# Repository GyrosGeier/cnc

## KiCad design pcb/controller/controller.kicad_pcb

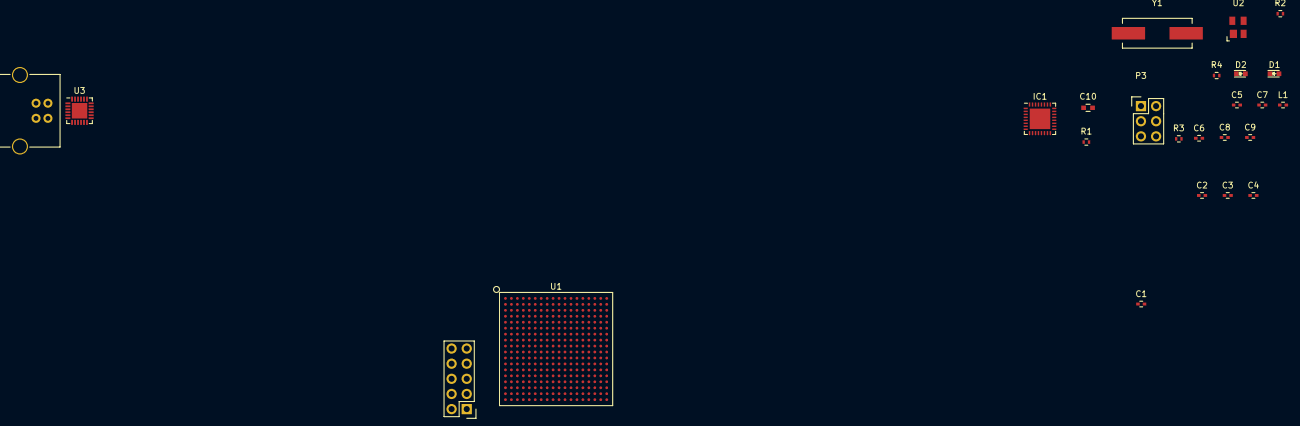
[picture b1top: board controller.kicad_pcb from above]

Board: 2 copper layers, 25 parts (0 on the bottom side), 25 nets, no tracks yet.

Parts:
C1, C2, C3, C4, C5, C6, C8: 100n; C_0402
C7, C9: 18pF; C_0402
C10: 4,7u; C_0603
D1, D2: orange; LED_0603
IC1: ATMEGA328P-M; QFN-32-1EP_5x5mm_Pitch0.5mm
L1: 1u; C_0402
P1: CONN_02X05; Pin_Header_Straight_2x05
P2: USB_B
P3: CONN_02X03; Pin_Header_Straight_2x03
R1, R2: 10k; R_0402
R3, R4: 60; R_0402
U1: EPM2210F324; BGA-324-1mm
U2: DRTR5V0U2SR; SOT-143
U3: CP2104; QFN-24-1EP_4x4mm_Pitch0.5mm
Y1: 16 MHz/18pF; Crystal_HC49-SD_SMD

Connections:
+3V3: C1.1, C2.1, C3.1, C4.1, C5.1, IC1.4, IC1.6, L1.1, P1.4, P3.2, R1.1, R2.2, R3.1, R4.1, U1.C1, U1.J7, U1.K7, U1.T1, U3.5
/GRBL/Arduino/0: IC1.30, U3.21
/GRBL/Arduino/1: IC1.31, U3.20
/GRBL/Arduino/DTR: C8.2, U3.23
/GRBL/Arduino/USB_D+: P2.3, U2.3, U3.3
/GRBL/Arduino/USB_D-: P2.2, U2.2, U3.4
/GRBL/Arduino/USB_VCC: P2.1, U2.4, U3.7, U3.8
/GRBL/Arduino/XI: C7.1, IC1.7, Y1.1
/GRBL/Arduino/XO: C9.1, IC1.8, Y1.2
/GRBL/SPINDLE_DIR: IC1.17, P3.3
/GRBL/SPINDLE_PWM: IC1.15, P3.4
/GRBL/Z_LIMIT: IC1.16, P3.1
/GRBL/~PGM_RESET: C8.1, P3.5, R1.2
/TCK: P1.1, U1.R4
/TDI: P1.9, U1.M7
/TDO: P1.3, U1.N6
/TMS: P1.5, U1.P5
GND: C1.2, C2.2, C3.2, C4.2, C5.2, C6.2, C7.2, C9.2, C10.2, IC1.3, IC1.5, IC1.21, P1.2, P1.10, P2.4, P3.6, U2.1, U3.2
unnamed: C6.1, IC1.18, L1.2
unnamed: C10.1, U3.16
unnamed: D1.1, U3.13
unnamed: D1.2, R3.2
unnamed: D2.1, U3.14
unnamed: D2.2, R4.2
unnamed: R2.1, U3.9

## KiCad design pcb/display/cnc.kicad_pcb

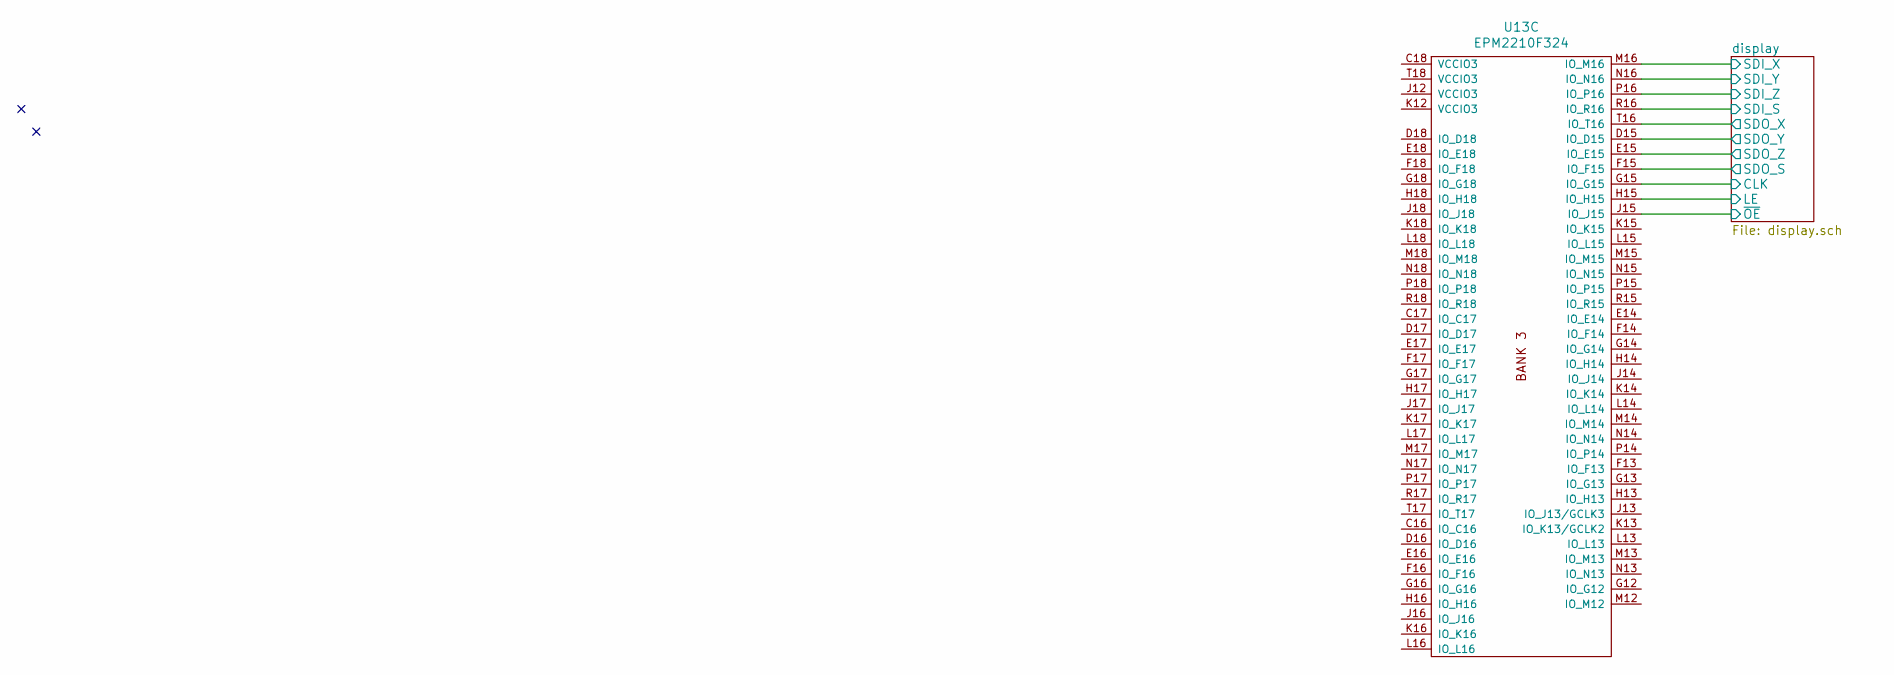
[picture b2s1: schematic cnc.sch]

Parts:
U13: EPM2210F324

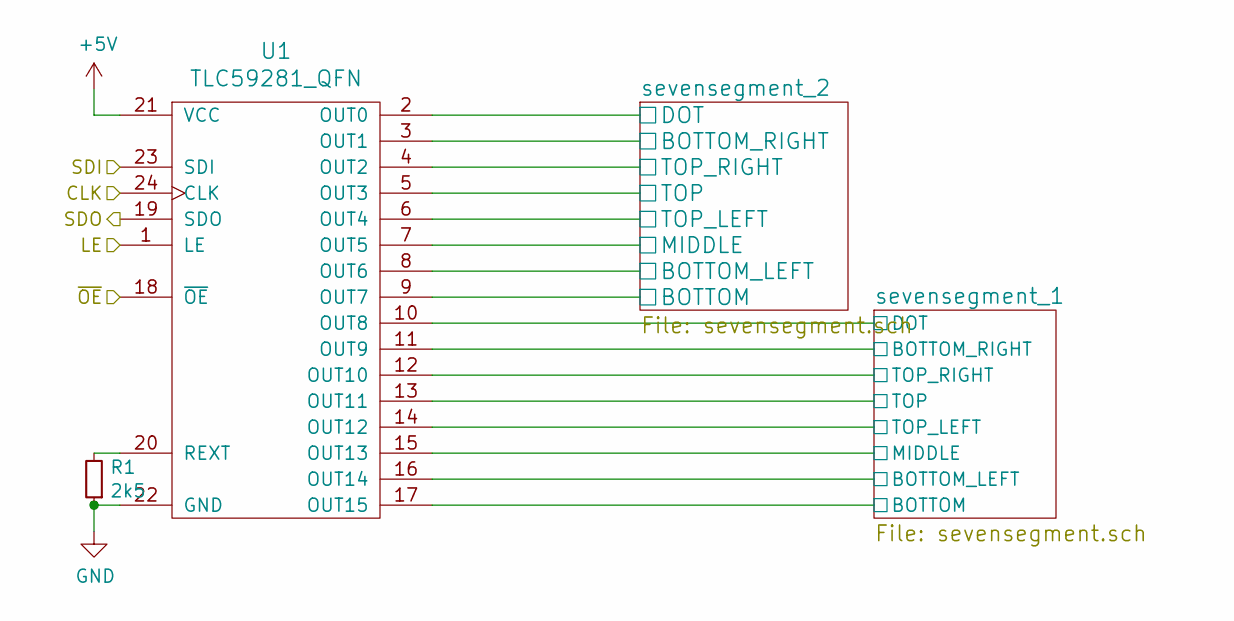
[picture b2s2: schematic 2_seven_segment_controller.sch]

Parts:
R1: 2k5; R_0603
U1: TLC59281_QFN; QFN-24-1EP_4x4mm_Pitch0.5mm

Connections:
+5V: U1.21 (VCC); also elsewhere on the board
/display/CLK: U1.24 (CLK); also elsewhere on the board
/display/LE: U1.1 (LE); also elsewhere on the board
/display/SDI_X: U1.23 (SDI)
/display/display_x1_x2/sevensegment_1/BOTTOM: U1.17 (OUT15); also elsewhere on the board
/display/display_x1_x2/sevensegment_1/BOTTOM_LEFT: U1.16 (OUT14); also elsewhere on the board
/display/display_x1_x2/sevensegment_1/BOTTOM_RIGHT: U1.11 (OUT9); also elsewhere on the board
/display/display_x1_x2/sevensegment_1/DOT: U1.10 (OUT8); also elsewhere on the board
/display/display_x1_x2/sevensegment_1/MIDDLE: U1.15 (OUT13); also elsewhere on the board
/display/display_x1_x2/sevensegment_1/TOP: U1.13 (OUT11); also elsewhere on the board
/display/display_x1_x2/sevensegment_1/TOP_LEFT: U1.14 (OUT12); also elsewhere on the board
/display/display_x1_x2/sevensegment_1/TOP_RIGHT: U1.12 (OUT10); also elsewhere on the board
/display/display_x1_x2/sevensegment_2/BOTTOM: U1.9 (OUT7); also elsewhere on the board
/display/display_x1_x2/sevensegment_2/BOTTOM_LEFT: U1.8 (OUT6); also elsewhere on the board
/display/display_x1_x2/sevensegment_2/BOTTOM_RIGHT: U1.3 (OUT1); also elsewhere on the board
/display/display_x1_x2/sevensegment_2/DOT: U1.2 (OUT0); also elsewhere on the board
/display/display_x1_x2/sevensegment_2/MIDDLE: U1.7 (OUT5); also elsewhere on the board
/display/display_x1_x2/sevensegment_2/TOP: U1.5 (OUT3); also elsewhere on the board
/display/display_x1_x2/sevensegment_2/TOP_LEFT: U1.6 (OUT4); also elsewhere on the board
/display/display_x1_x2/sevensegment_2/TOP_RIGHT: U1.4 (OUT2); also elsewhere on the board
/display/display_x3_x4/SDI: U1.19 (SDO); also elsewhere on the board
/display/~OE: U1.18 (~OE); also elsewhere on the board
GND: R1.1, U1.22 (GND); also elsewhere on the board
unnamed: R1.2, U1.20 (REXT)

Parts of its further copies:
R2, R3, R4, R5, R6, R7, R8, R9, R10, R11, R12: 2k5; R_0603
U2, U3, U4, U5, U6, U7, U8, U9, U10, U11, U12: TLC59281_QFN; QFN-24-1EP_4x4mm_Pitch0.5mm

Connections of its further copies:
+5V: U2.21 (VCC), U3.21 (VCC), U4.21 (VCC), U5.21 (VCC), U6.21 (VCC), U7.21 (VCC), U8.21 (VCC), U9.21 (VCC), U10.21 (VCC), U11.21 (VCC), U12.21 (VCC); also elsewhere on the board
/display/CLK: U2.24 (CLK), U3.24 (CLK), U4.24 (CLK), U5.24 (CLK), U6.24 (CLK), U7.24 (CLK), U8.24 (CLK), U9.24 (CLK), U10.24 (CLK), U11.24 (CLK), U12.24 (CLK); also elsewhere on the board
/display/LE: U2.1 (LE), U3.1 (LE), U4.1 (LE), U5.1 (LE), U6.1 (LE), U7.1 (LE), U8.1 (LE), U9.1 (LE), U10.1 (LE), U11.1 (LE), U12.1 (LE); also elsewhere on the board
/display/SDI_S: U10.23 (SDI)
/display/SDI_Y: U4.23 (SDI)
/display/SDI_Z: U7.23 (SDI)
/display/SDO_S: U12.19 (SDO)
/display/SDO_X: U3.19 (SDO)
/display/SDO_Y: U6.19 (SDO)
/display/SDO_Z: U9.19 (SDO)
/display/display_s1_s2/sevensegment_1/BOTTOM: U10.17 (OUT15); also elsewhere on the board
/display/display_s1_s2/sevensegment_1/BOTTOM_LEFT: U10.16 (OUT14); also elsewhere on the board
/display/display_s1_s2/sevensegment_1/BOTTOM_RIGHT: U10.11 (OUT9); also elsewhere on the board
/display/display_s1_s2/sevensegment_1/DOT: U10.10 (OUT8); also elsewhere on the board
/display/display_s1_s2/sevensegment_1/MIDDLE: U10.15 (OUT13); also elsewhere on the board
/display/display_s1_s2/sevensegment_1/TOP: U10.13 (OUT11); also elsewhere on the board
/display/display_s1_s2/sevensegment_1/TOP_LEFT: U10.14 (OUT12); also elsewhere on the board
/display/display_s1_s2/sevensegment_1/TOP_RIGHT: U10.12 (OUT10); also elsewhere on the board
/display/display_s1_s2/sevensegment_2/BOTTOM: U10.9 (OUT7); also elsewhere on the board
/display/display_s1_s2/sevensegment_2/BOTTOM_LEFT: U10.8 (OUT6); also elsewhere on the board
/display/display_s1_s2/sevensegment_2/BOTTOM_RIGHT: U10.3 (OUT1); also elsewhere on the board
/display/display_s1_s2/sevensegment_2/DOT: U10.2 (OUT0); also elsewhere on the board
/display/display_s1_s2/sevensegment_2/MIDDLE: U10.7 (OUT5); also elsewhere on the board
/display/display_s1_s2/sevensegment_2/TOP: U10.5 (OUT3); also elsewhere on the board
/display/display_s1_s2/sevensegment_2/TOP_LEFT: U10.6 (OUT4); also elsewhere on the board
/display/display_s1_s2/sevensegment_2/TOP_RIGHT: U10.4 (OUT2); also elsewhere on the board
/display/display_s3_s4/SDI: U8.19 (SDO), U9.23 (SDI)
/display/display_s3_s4/sevensegment_1/BOTTOM: U9.17 (OUT15); also elsewhere on the board
/display/display_s3_s4/sevensegment_1/BOTTOM_LEFT: U9.16 (OUT14); also elsewhere on the board
/display/display_s3_s4/sevensegment_1/BOTTOM_RIGHT: U9.11 (OUT9); also elsewhere on the board
/display/display_s3_s4/sevensegment_1/DOT: U9.10 (OUT8); also elsewhere on the board
/display/display_s3_s4/sevensegment_1/MIDDLE: U9.15 (OUT13); also elsewhere on the board
/display/display_s3_s4/sevensegment_1/TOP: U9.13 (OUT11); also elsewhere on the board
/display/display_s3_s4/sevensegment_1/TOP_LEFT: U9.14 (OUT12); also elsewhere on the board
/display/display_s3_s4/sevensegment_1/TOP_RIGHT: U9.12 (OUT10); also elsewhere on the board
/display/display_s3_s4/sevensegment_2/BOTTOM: U9.9 (OUT7); also elsewhere on the board
/display/display_s3_s4/sevensegment_2/BOTTOM_LEFT: U9.8 (OUT6); also elsewhere on the board
/display/display_s3_s4/sevensegment_2/BOTTOM_RIGHT: U9.3 (OUT1); also elsewhere on the board
/display/display_s3_s4/sevensegment_2/DOT: U9.2 (OUT0); also elsewhere on the board
/display/display_s3_s4/sevensegment_2/MIDDLE: U9.7 (OUT5); also elsewhere on the board
/display/display_s3_s4/sevensegment_2/TOP: U9.5 (OUT3); also elsewhere on the board
/display/display_s3_s4/sevensegment_2/TOP_LEFT: U9.6 (OUT4); also elsewhere on the board
/display/display_s3_s4/sevensegment_2/TOP_RIGHT: U9.4 (OUT2); also elsewhere on the board
/display/display_s/SDI: U11.19 (SDO), U12.23 (SDI)
/display/display_s/sevensegment_1/BOTTOM: U12.17 (OUT15); also elsewhere on the board
/display/display_s/sevensegment_1/BOTTOM_LEFT: U12.16 (OUT14); also elsewhere on the board
/display/display_s/sevensegment_1/BOTTOM_RIGHT: U12.11 (OUT9); also elsewhere on the board
/display/display_s/sevensegment_1/DOT: U12.10 (OUT8); also elsewhere on the board
/display/display_s/sevensegment_1/MIDDLE: U12.15 (OUT13); also elsewhere on the board
/display/display_s/sevensegment_1/TOP: U12.13 (OUT11); also elsewhere on the board
/display/display_s/sevensegment_1/TOP_LEFT: U12.14 (OUT12); also elsewhere on the board
/display/display_s/sevensegment_1/TOP_RIGHT: U12.12 (OUT10); also elsewhere on the board
/display/display_s/sevensegment_2/BOTTOM: U12.9 (OUT7); also elsewhere on the board
/display/display_s/sevensegment_2/BOTTOM_LEFT: U12.8 (OUT6); also elsewhere on the board
/display/display_s/sevensegment_2/BOTTOM_RIGHT: U12.3 (OUT1); also elsewhere on the board
/display/display_s/sevensegment_2/DOT: U12.2 (OUT0); also elsewhere on the board
/display/display_s/sevensegment_2/MIDDLE: U12.7 (OUT5); also elsewhere on the board
/display/display_s/sevensegment_2/TOP: U12.5 (OUT3); also elsewhere on the board
/display/display_s/sevensegment_2/TOP_LEFT: U12.6 (OUT4); also elsewhere on the board
/display/display_s/sevensegment_2/TOP_RIGHT: U12.4 (OUT2); also elsewhere on the board
/display/display_x3_x4/SDI: U2.23 (SDI); also elsewhere on the board
/display/display_x3_x4/sevensegment_1/BOTTOM: U2.17 (OUT15); also elsewhere on the board
/display/display_x3_x4/sevensegment_1/BOTTOM_LEFT: U2.16 (OUT14); also elsewhere on the board
/display/display_x3_x4/sevensegment_1/BOTTOM_RIGHT: U2.11 (OUT9); also elsewhere on the board
/display/display_x3_x4/sevensegment_1/DOT: U2.10 (OUT8); also elsewhere on the board
/display/display_x3_x4/sevensegment_1/MIDDLE: U2.15 (OUT13); also elsewhere on the board
/display/display_x3_x4/sevensegment_1/TOP: U2.13 (OUT11); also elsewhere on the board
/display/display_x3_x4/sevensegment_1/TOP_LEFT: U2.14 (OUT12); also elsewhere on the board
/display/display_x3_x4/sevensegment_1/TOP_RIGHT: U2.12 (OUT10); also elsewhere on the board
/display/display_x3_x4/sevensegment_2/BOTTOM: U2.9 (OUT7); also elsewhere on the board
/display/display_x3_x4/sevensegment_2/BOTTOM_LEFT: U2.8 (OUT6); also elsewhere on the board
/display/display_x3_x4/sevensegment_2/BOTTOM_RIGHT: U2.3 (OUT1); also elsewhere on the board
/display/display_x3_x4/sevensegment_2/DOT: U2.2 (OUT0); also elsewhere on the board
/display/display_x3_x4/sevensegment_2/MIDDLE: U2.7 (OUT5); also elsewhere on the board
/display/display_x3_x4/sevensegment_2/TOP: U2.5 (OUT3); also elsewhere on the board
/display/display_x3_x4/sevensegment_2/TOP_LEFT: U2.6 (OUT4); also elsewhere on the board
/display/display_x3_x4/sevensegment_2/TOP_RIGHT: U2.4 (OUT2); also elsewhere on the board
/display/display_x5_y5/SDI: U2.19 (SDO), U3.23 (SDI)
/display/display_x5_y5/sevensegment_1/BOTTOM: U3.17 (OUT15); also elsewhere on the board
/display/display_x5_y5/sevensegment_1/BOTTOM_LEFT: U3.16 (OUT14); also elsewhere on the board
/display/display_x5_y5/sevensegment_1/BOTTOM_RIGHT: U3.11 (OUT9); also elsewhere on the board
/display/display_x5_y5/sevensegment_1/DOT: U3.10 (OUT8); also elsewhere on the board
/display/display_x5_y5/sevensegment_1/MIDDLE: U3.15 (OUT13); also elsewhere on the board
/display/display_x5_y5/sevensegment_1/TOP: U3.13 (OUT11); also elsewhere on the board
/display/display_x5_y5/sevensegment_1/TOP_LEFT: U3.14 (OUT12); also elsewhere on the board
/display/display_x5_y5/sevensegment_1/TOP_RIGHT: U3.12 (OUT10); also elsewhere on the board
/display/display_x5_y5/sevensegment_2/BOTTOM: U3.9 (OUT7); also elsewhere on the board
/display/display_x5_y5/sevensegment_2/BOTTOM_LEFT: U3.8 (OUT6); also elsewhere on the board
/display/display_x5_y5/sevensegment_2/BOTTOM_RIGHT: U3.3 (OUT1); also elsewhere on the board
/display/display_x5_y5/sevensegment_2/DOT: U3.2 (OUT0); also elsewhere on the board
/display/display_x5_y5/sevensegment_2/MIDDLE: U3.7 (OUT5); also elsewhere on the board
/display/display_x5_y5/sevensegment_2/TOP: U3.5 (OUT3); also elsewhere on the board
/display/display_x5_y5/sevensegment_2/TOP_LEFT: U3.6 (OUT4); also elsewhere on the board
/display/display_x5_y5/sevensegment_2/TOP_RIGHT: U3.4 (OUT2); also elsewhere on the board
/display/display_y1_y2/SDI: U4.19 (SDO), U5.23 (SDI)
/display/display_y1_y2/sevensegment_1/BOTTOM: U5.17 (OUT15); also elsewhere on the board
/display/display_y1_y2/sevensegment_1/BOTTOM_LEFT: U5.16 (OUT14); also elsewhere on the board
/display/display_y1_y2/sevensegment_1/BOTTOM_RIGHT: U5.11 (OUT9); also elsewhere on the board
/display/display_y1_y2/sevensegment_1/DOT: U5.10 (OUT8); also elsewhere on the board
/display/display_y1_y2/sevensegment_1/MIDDLE: U5.15 (OUT13); also elsewhere on the board
/display/display_y1_y2/sevensegment_1/TOP: U5.13 (OUT11); also elsewhere on the board
/display/display_y1_y2/sevensegment_1/TOP_LEFT: U5.14 (OUT12); also elsewhere on the board
/display/display_y1_y2/sevensegment_1/TOP_RIGHT: U5.12 (OUT10); also elsewhere on the board
/display/display_y1_y2/sevensegment_2/BOTTOM: U5.9 (OUT7); also elsewhere on the board
/display/display_y1_y2/sevensegment_2/BOTTOM_LEFT: U5.8 (OUT6); also elsewhere on the board
/display/display_y1_y2/sevensegment_2/BOTTOM_RIGHT: U5.3 (OUT1); also elsewhere on the board
/display/display_y1_y2/sevensegment_2/DOT: U5.2 (OUT0); also elsewhere on the board
/display/display_y1_y2/sevensegment_2/MIDDLE: U5.7 (OUT5); also elsewhere on the board
/display/display_y1_y2/sevensegment_2/TOP: U5.5 (OUT3); also elsewhere on the board
/display/display_y1_y2/sevensegment_2/TOP_LEFT: U5.6 (OUT4); also elsewhere on the board
/display/display_y1_y2/sevensegment_2/TOP_RIGHT: U5.4 (OUT2); also elsewhere on the board
/display/display_y3_y4/sevensegment_1/BOTTOM: U4.17 (OUT15); also elsewhere on the board
/display/display_y3_y4/sevensegment_1/BOTTOM_LEFT: U4.16 (OUT14); also elsewhere on the board
/display/display_y3_y4/sevensegment_1/BOTTOM_RIGHT: U4.11 (OUT9); also elsewhere on the board
/display/display_y3_y4/sevensegment_1/DOT: U4.10 (OUT8); also elsewhere on the board
/display/display_y3_y4/sevensegment_1/MIDDLE: U4.15 (OUT13); also elsewhere on the board
/display/display_y3_y4/sevensegment_1/TOP: U4.13 (OUT11); also elsewhere on the board
/display/display_y3_y4/sevensegment_1/TOP_LEFT: U4.14 (OUT12); also elsewhere on the board
/display/display_y3_y4/sevensegment_1/TOP_RIGHT: U4.12 (OUT10); also elsewhere on the board
/display/display_y3_y4/sevensegment_2/BOTTOM: U4.9 (OUT7); also elsewhere on the board
/display/display_y3_y4/sevensegment_2/BOTTOM_LEFT: U4.8 (OUT6); also elsewhere on the board
/display/display_y3_y4/sevensegment_2/BOTTOM_RIGHT: U4.3 (OUT1); also elsewhere on the board
/display/display_y3_y4/sevensegment_2/DOT: U4.2 (OUT0); also elsewhere on the board
/display/display_y3_y4/sevensegment_2/MIDDLE: U4.7 (OUT5); also elsewhere on the board
/display/display_y3_y4/sevensegment_2/TOP: U4.5 (OUT3); also elsewhere on the board
/display/display_y3_y4/sevensegment_2/TOP_LEFT: U4.6 (OUT4); also elsewhere on the board
/display/display_y3_y4/sevensegment_2/TOP_RIGHT: U4.4 (OUT2); also elsewhere on the board
/display/display_y/SDI: U10.19 (SDO), U11.23 (SDI)
/display/display_y/sevensegment_1/BOTTOM: U11.17 (OUT15); also elsewhere on the board
/display/display_y/sevensegment_1/BOTTOM_LEFT: U11.16 (OUT14); also elsewhere on the board
/display/display_y/sevensegment_1/BOTTOM_RIGHT: U11.11 (OUT9); also elsewhere on the board
/display/display_y/sevensegment_1/DOT: U11.10 (OUT8); also elsewhere on the board
/display/display_y/sevensegment_1/MIDDLE: U11.15 (OUT13); also elsewhere on the board
/display/display_y/sevensegment_1/TOP: U11.13 (OUT11); also elsewhere on the board
/display/display_y/sevensegment_1/TOP_LEFT: U11.14 (OUT12); also elsewhere on the board
/display/display_y/sevensegment_1/TOP_RIGHT: U11.12 (OUT10); also elsewhere on the board
/display/display_y/sevensegment_2/BOTTOM: U11.9 (OUT7); also elsewhere on the board
/display/display_y/sevensegment_2/BOTTOM_LEFT: U11.8 (OUT6); also elsewhere on the board
/display/display_y/sevensegment_2/BOTTOM_RIGHT: U11.3 (OUT1); also elsewhere on the board
/display/display_y/sevensegment_2/DOT: U11.2 (OUT0); also elsewhere on the board
/display/display_y/sevensegment_2/MIDDLE: U11.7 (OUT5); also elsewhere on the board
/display/display_y/sevensegment_2/TOP: U11.5 (OUT3); also elsewhere on the board
/display/display_y/sevensegment_2/TOP_LEFT: U11.6 (OUT4); also elsewhere on the board
/display/display_y/sevensegment_2/TOP_RIGHT: U11.4 (OUT2); also elsewhere on the board
/display/display_z1_z2/SDI: U5.19 (SDO), U6.23 (SDI)
/display/display_z1_z2/sevensegment_1/BOTTOM: U6.17 (OUT15); also elsewhere on the board
/display/display_z1_z2/sevensegment_1/BOTTOM_LEFT: U6.16 (OUT14); also elsewhere on the board
/display/display_z1_z2/sevensegment_1/BOTTOM_RIGHT: U6.11 (OUT9); also elsewhere on the board
/display/display_z1_z2/sevensegment_1/DOT: U6.10 (OUT8); also elsewhere on the board
/display/display_z1_z2/sevensegment_1/MIDDLE: U6.15 (OUT13); also elsewhere on the board
/display/display_z1_z2/sevensegment_1/TOP: U6.13 (OUT11); also elsewhere on the board
/display/display_z1_z2/sevensegment_1/TOP_LEFT: U6.14 (OUT12); also elsewhere on the board
/display/display_z1_z2/sevensegment_1/TOP_RIGHT: U6.12 (OUT10); also elsewhere on the board
/display/display_z1_z2/sevensegment_2/BOTTOM: U6.9 (OUT7); also elsewhere on the board
/display/display_z1_z2/sevensegment_2/BOTTOM_LEFT: U6.8 (OUT6); also elsewhere on the board
/display/display_z1_z2/sevensegment_2/BOTTOM_RIGHT: U6.3 (OUT1); also elsewhere on the board
/display/display_z1_z2/sevensegment_2/DOT: U6.2 (OUT0); also elsewhere on the board
/display/display_z1_z2/sevensegment_2/MIDDLE: U6.7 (OUT5); also elsewhere on the board
/display/display_z1_z2/sevensegment_2/TOP: U6.5 (OUT3); also elsewhere on the board
/display/display_z1_z2/sevensegment_2/TOP_LEFT: U6.6 (OUT4); also elsewhere on the board
/display/display_z1_z2/sevensegment_2/TOP_RIGHT: U6.4 (OUT2); also elsewhere on the board
/display/display_z3_z4/sevensegment_1/BOTTOM: U7.17 (OUT15); also elsewhere on the board
/display/display_z3_z4/sevensegment_1/BOTTOM_LEFT: U7.16 (OUT14); also elsewhere on the board
/display/display_z3_z4/sevensegment_1/BOTTOM_RIGHT: U7.11 (OUT9); also elsewhere on the board
/display/display_z3_z4/sevensegment_1/DOT: U7.10 (OUT8); also elsewhere on the board
/display/display_z3_z4/sevensegment_1/MIDDLE: U7.15 (OUT13); also elsewhere on the board
/display/display_z3_z4/sevensegment_1/TOP: U7.13 (OUT11); also elsewhere on the board
/display/display_z3_z4/sevensegment_1/TOP_LEFT: U7.14 (OUT12); also elsewhere on the board
/display/display_z3_z4/sevensegment_1/TOP_RIGHT: U7.12 (OUT10); also elsewhere on the board
/display/display_z3_z4/sevensegment_2/BOTTOM: U7.9 (OUT7); also elsewhere on the board
/display/display_z3_z4/sevensegment_2/BOTTOM_LEFT: U7.8 (OUT6); also elsewhere on the board
/display/display_z3_z4/sevensegment_2/BOTTOM_RIGHT: U7.3 (OUT1); also elsewhere on the board
/display/display_z3_z4/sevensegment_2/DOT: U7.2 (OUT0); also elsewhere on the board
/display/display_z3_z4/sevensegment_2/MIDDLE: U7.7 (OUT5); also elsewhere on the board
/display/display_z3_z4/sevensegment_2/TOP: U7.5 (OUT3); also elsewhere on the board
/display/display_z3_z4/sevensegment_2/TOP_LEFT: U7.6 (OUT4); also elsewhere on the board
/display/display_z3_z4/sevensegment_2/TOP_RIGHT: U7.4 (OUT2); also elsewhere on the board
/display/display_z5_s5/SDI: U7.19 (SDO), U8.23 (SDI)
/display/display_z5_s5/sevensegment_1/BOTTOM: U8.17 (OUT15); also elsewhere on the board
/display/display_z5_s5/sevensegment_1/BOTTOM_LEFT: U8.16 (OUT14); also elsewhere on the board
/display/display_z5_s5/sevensegment_1/BOTTOM_RIGHT: U8.11 (OUT9); also elsewhere on the board
/display/display_z5_s5/sevensegment_1/DOT: U8.10 (OUT8); also elsewhere on the board
/display/display_z5_s5/sevensegment_1/MIDDLE: U8.15 (OUT13); also elsewhere on the board
/display/display_z5_s5/sevensegment_1/TOP: U8.13 (OUT11); also elsewhere on the board
/display/display_z5_s5/sevensegment_1/TOP_LEFT: U8.14 (OUT12); also elsewhere on the board
/display/display_z5_s5/sevensegment_1/TOP_RIGHT: U8.12 (OUT10); also elsewhere on the board
/display/display_z5_s5/sevensegment_2/BOTTOM: U8.9 (OUT7); also elsewhere on the board
/display/display_z5_s5/sevensegment_2/BOTTOM_LEFT: U8.8 (OUT6); also elsewhere on the board
/display/display_z5_s5/sevensegment_2/BOTTOM_RIGHT: U8.3 (OUT1); also elsewhere on the board
/display/display_z5_s5/sevensegment_2/DOT: U8.2 (OUT0); also elsewhere on the board
/display/display_z5_s5/sevensegment_2/MIDDLE: U8.7 (OUT5); also elsewhere on the board
/display/display_z5_s5/sevensegment_2/TOP: U8.5 (OUT3); also elsewhere on the board
/display/display_z5_s5/sevensegment_2/TOP_LEFT: U8.6 (OUT4); also elsewhere on the board
/display/display_z5_s5/sevensegment_2/TOP_RIGHT: U8.4 (OUT2); also elsewhere on the board
/display/~OE: U2.18 (~OE), U3.18 (~OE), U4.18 (~OE), U5.18 (~OE), U6.18 (~OE), U7.18 (~OE), U8.18 (~OE), U9.18 (~OE), U10.18 (~OE), U11.18 (~OE), U12.18 (~OE); also elsewhere on the board
GND: R2.1, R3.1, R4.1, R5.1, R6.1, R7.1, R8.1, R9.1, R10.1, R11.1, R12.1, U2.22 (GND), U3.22 (GND), U4.22 (GND), U5.22 (GND), U6.22 (GND), U7.22 (GND), U8.22 (GND), U9.22 (GND), U10.22 (GND), U11.22 (GND), U12.22 (GND); also elsewhere on the board
unnamed: R2.2, U2.20 (REXT)
unnamed: R3.2, U3.20 (REXT)
unnamed: R4.2, U4.20 (REXT)
unnamed: R5.2, U5.20 (REXT)
unnamed: R6.2, U6.20 (REXT)
unnamed: R7.2, U7.20 (REXT)
unnamed: R8.2, U8.20 (REXT)
unnamed: R9.2, U9.20 (REXT)
unnamed: R10.2, U10.20 (REXT)
unnamed: R11.2, U11.20 (REXT)
unnamed: R12.2, U12.20 (REXT)
